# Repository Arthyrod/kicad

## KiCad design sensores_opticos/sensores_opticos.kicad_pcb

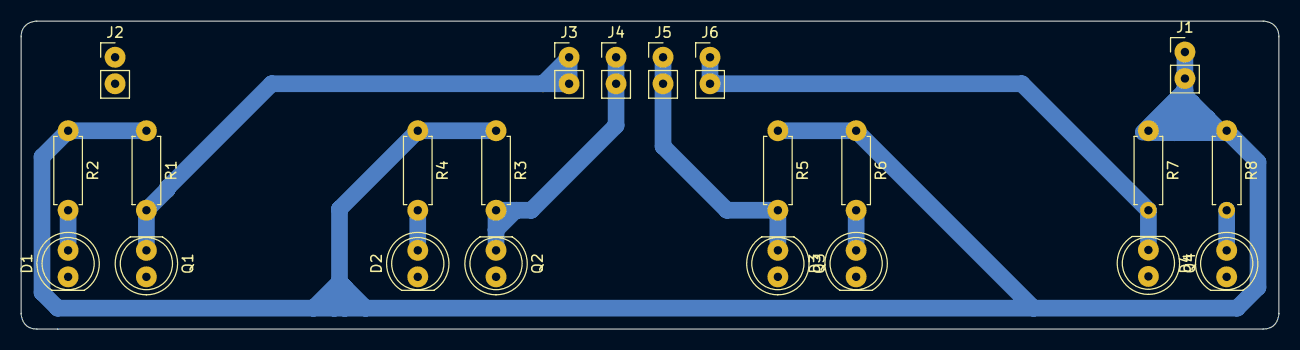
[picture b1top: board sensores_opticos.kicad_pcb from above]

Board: 2 copper layers, 120.5 x 29.5 mm, 22 parts (0 on the bottom side), 10 nets.

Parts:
D1, D2, D3, D4: LED; LED_D5.0mm
J1, J2, J3, J4, J5, J6: Conn_01x02_Pin; PinHeader_1x02_P2.54mm_Vertical
Q1, Q2, Q3, Q4: BPW40; LED_D5.0mm_Clear
R1, R2, R3, R4, R5, R6, R7, R8: R; R_Axial_DIN0207_L6.3mm_D2.5mm_P7.62mm_Horizontal

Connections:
+5V: J1.1, J1.2, R1.1, R2.1, R3.1, R4.1, R5.1, R6.1, R7.1, R8.1
GND: D1.1 (K), D2.1 (K), D3.1 (K), D4.1 (K), J2.1, J2.2, Q1.2 (E), Q2.2 (E), Q3.2 (E), Q4.2 (E)
unnamed: D1.2 (A), R2.2
unnamed: D2.2 (A), R4.2
unnamed: D3.2 (A), R6.2
unnamed: D4.2 (A), R8.2
unnamed: J3.1, J3.2, Q1.1 (C), R1.2
unnamed: J4.1, J4.2, Q2.1 (C), R3.2
unnamed: J5.1, J5.2, Q3.1 (C), R5.2
unnamed: J6.1, J6.2, Q4.1 (C), R7.2

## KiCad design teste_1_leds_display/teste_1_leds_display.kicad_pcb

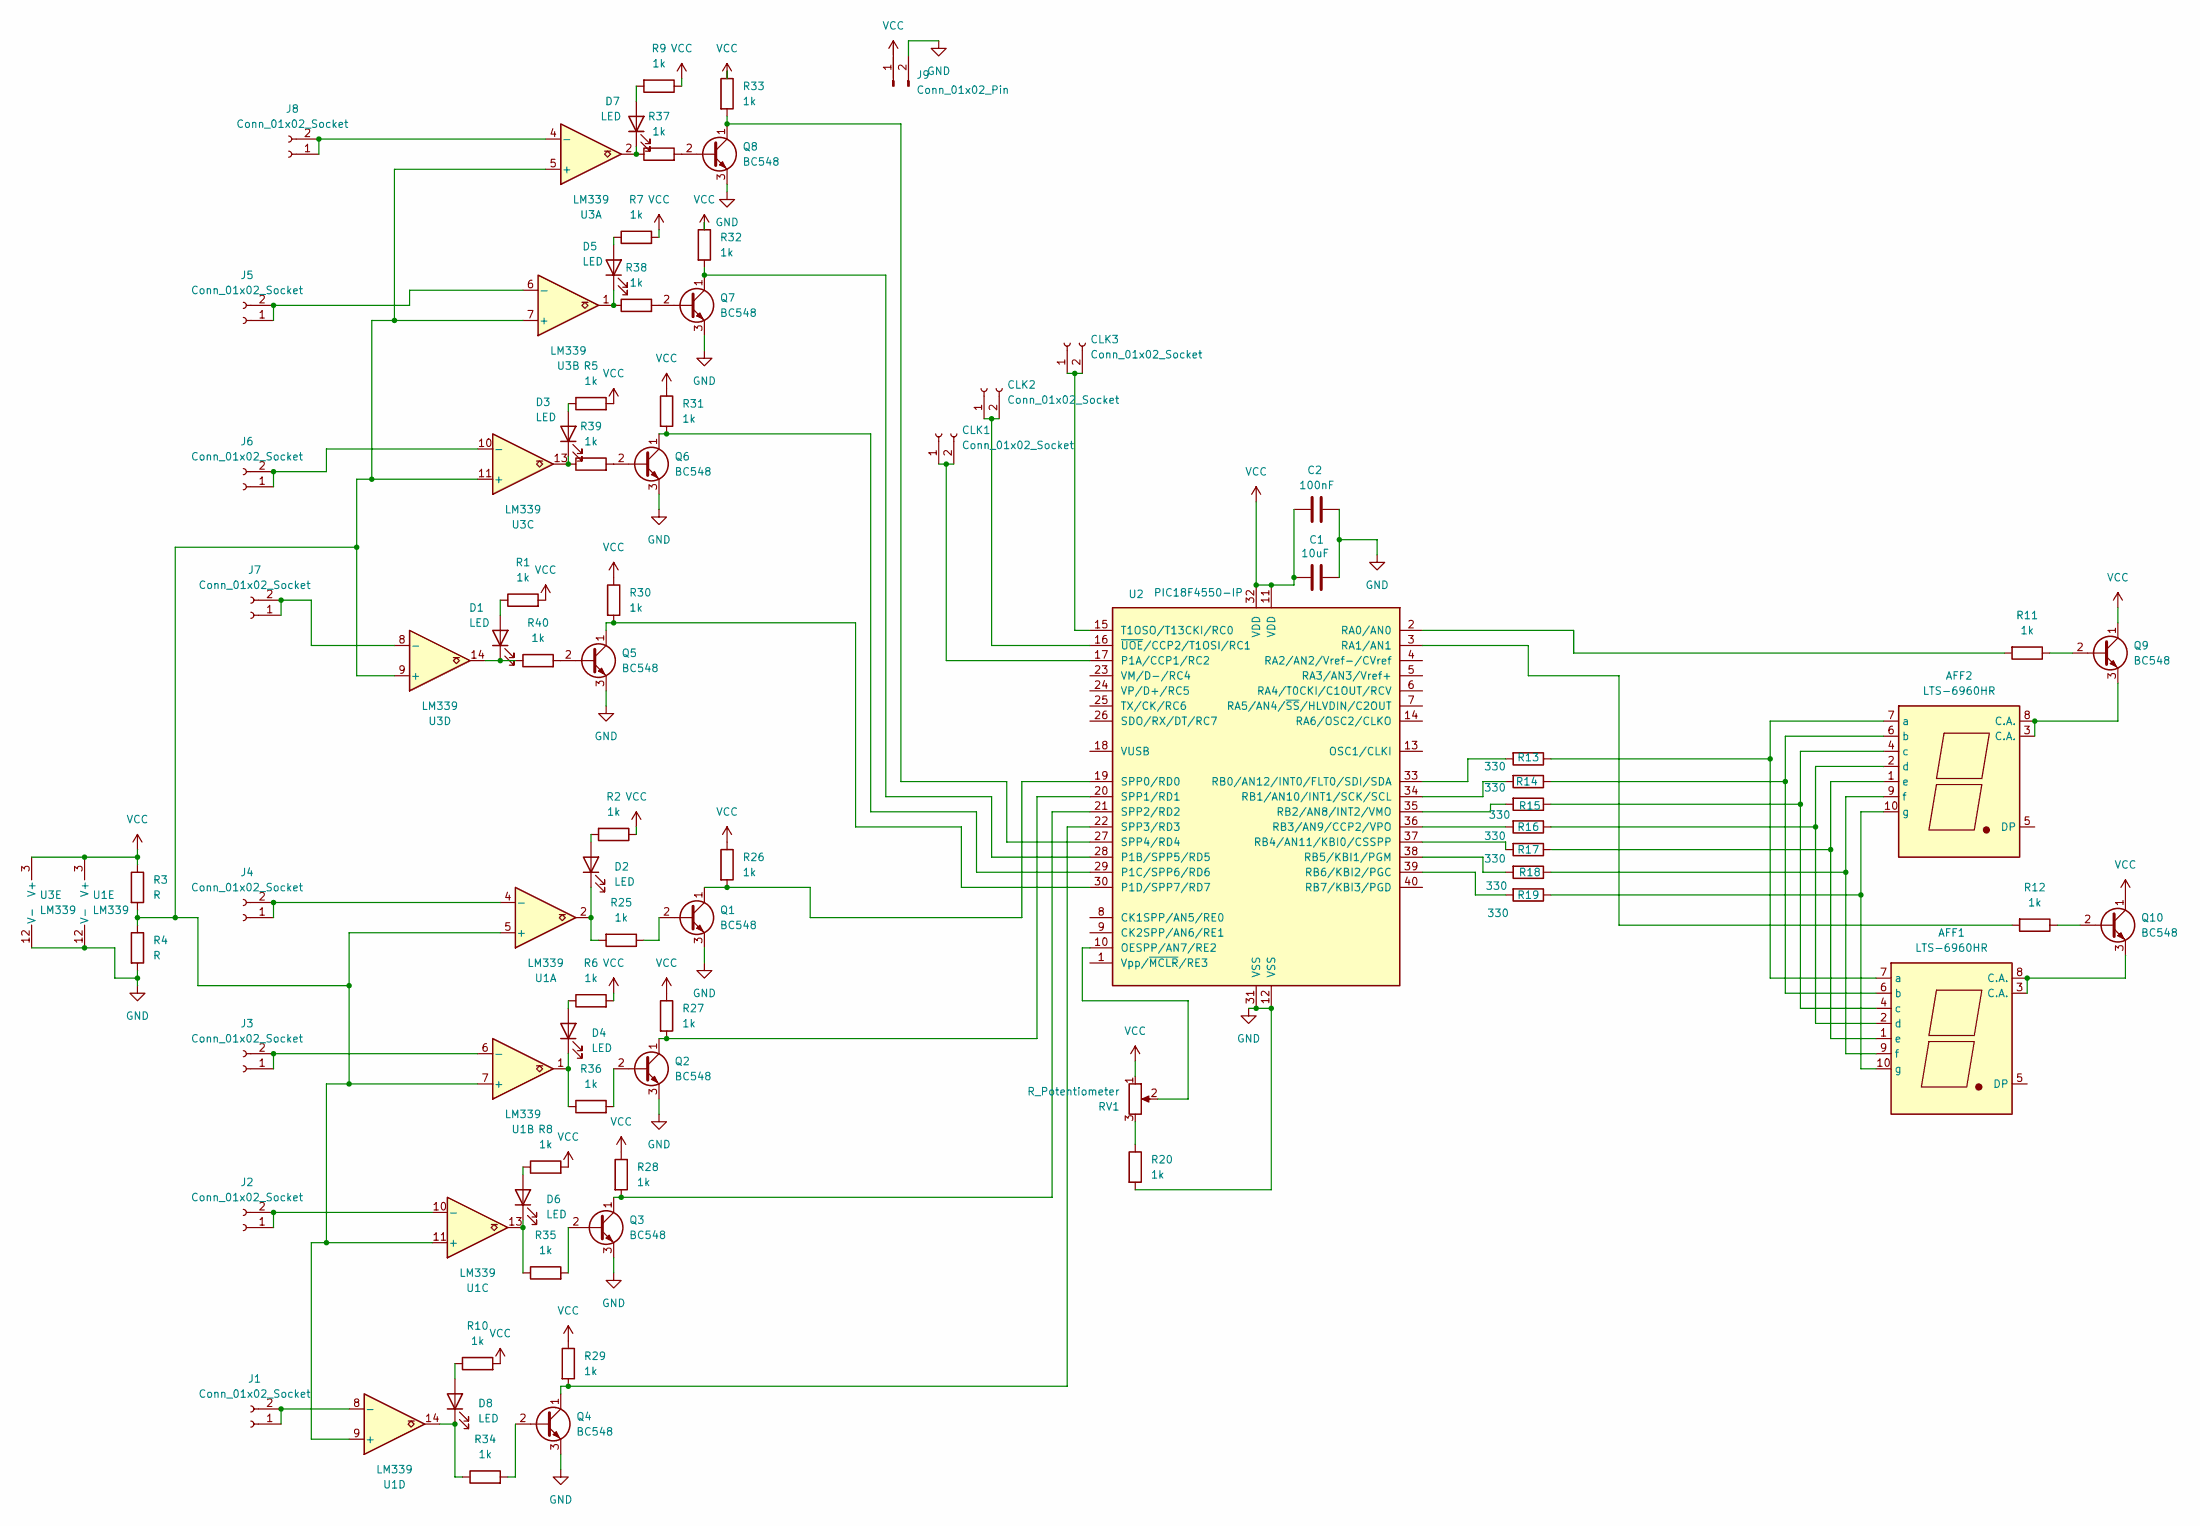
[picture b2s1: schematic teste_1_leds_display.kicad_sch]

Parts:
AFF1, AFF2: LTS-6960HR; 7SegmentLED_LTS6760_LTS6780
C1: 10uF; C_Axial_L5.1mm_D3.1mm_P7.50mm_Horizontal
C2: 100nF; C_Axial_L5.1mm_D3.1mm_P7.50mm_Horizontal
CLK1, CLK2, CLK3: Conn_01x02_Socket; PinSocket_1x02_P2.54mm_Vertical
D1, D2, D3, D4, D5, D6, D7, D8: LED; LED_D4.0mm
J1, J2, J3, J4, J5, J6, J7, J8: Conn_01x02_Socket; PinSocket_1x02_P2.54mm_Vertical
J9: Conn_01x02_Pin; PinHeader_1x02_P2.54mm_Vertical
Q1, Q2, Q3, Q4, Q5, Q6, Q7, Q8, Q9, Q10: BC548; TO-92_Wide
R1, R2, R5, R6, R7, R8, R9, R10, R11, R12, R20, R25, R26, R27, R28, R29, R30, R31, R32, R33, R34, R35, R36, R37, R38, R39, R40: 1k; R_Axial_DIN0207_L6.3mm_D2.5mm_P10.16mm_Horizontal
R3, R4: R; R_Axial_DIN0207_L6.3mm_D2.5mm_P10.16mm_Horizontal
R13, R14, R15, R16, R17, R18, R19: 330; R_Axial_DIN0207_L6.3mm_D2.5mm_P10.16mm_Horizontal
RV1: R_Potentiometer; Potentiometer_Alps_RK09K_Single_Vertical
U1, U3: LM339; DIP-14_W7.62mm
U2: PIC18F4550-IP; DIP-40_W15.24mm

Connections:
GND: C1.2, C2.2, J9.2, Q1.3 (E), Q2.3 (E), Q3.3 (E), Q4.3 (E), Q5.3 (E), Q6.3 (E), Q7.3 (E), Q8.3 (E), R4.2, R20.2, U1.12 (V-), U2.12 (VSS), U2.31 (VSS), U3.12 (V-)
unnamed: AFF1.7 (a), AFF2.7 (a), R13.1
unnamed: AFF1.6 (b), AFF2.6 (b), R14.1
unnamed: AFF1.4 (c), AFF2.4 (c), R15.1
unnamed: AFF1.2 (d), AFF2.2 (d), R16.1
unnamed: AFF1.1 (e), AFF2.1 (e), R17.1
unnamed: AFF1.9 (f), AFF2.9 (f), R18.1
unnamed: AFF1.10 (g), AFF2.10 (g), R19.1
unnamed 8: CLK1.1, CLK1.2, U2.17 (P1A/CCP1/RC2); also elsewhere on the board
unnamed 9: CLK2.1, CLK2.2, U2.16 (~UOE/CCP2/T1OSI/RC1); also elsewhere on the board
unnamed 10: CLK3.1, CLK3.2, U2.15 (T1OSO/T13CKI/RC0); also elsewhere on the board
unnamed: D1.2 (A), R1.1
unnamed: D1.1 (K), R40.1, U3.14
unnamed: D2.2 (A), R2.2
unnamed: D2.1 (K), R25.2, U1.2
unnamed: D3.2 (A), R5.1
unnamed: D3.1 (K), R39.1, U3.13
unnamed: D4.2 (A), R6.1
unnamed: D4.1 (K), R36.1, U1.1
unnamed: D5.2 (A), R7.1
unnamed: D5.1 (K), R38.1, U3.1
unnamed: D6.2 (A), R8.1
unnamed: D6.1 (K), R35.1, U1.13
unnamed: D7.2 (A), R9.2
unnamed: D7.1 (K), R37.1, U3.2
unnamed: D8.2 (A), R10.1
unnamed: D8.1 (K), R34.1, U1.14
unnamed: J1.1, J1.2, U1.8 (-)
unnamed: J2.1, J2.2, U1.10 (-)
unnamed: J3.1, J3.2, U1.6 (-)
unnamed: J4.1, J4.2, U1.4 (-)
unnamed: J5.1, J5.2, U3.6 (-)
unnamed: J6.1, J6.2, U3.10 (-)
unnamed: J7.1, J7.2, U3.8 (-)
unnamed: J8.1, J8.2, U3.4 (-)
unnamed: Q1.2 (B), R25.1
unnamed: Q1.1 (C), R26.2, U2.19 (SPP0/RD0)
unnamed: Q2.2 (B), R36.2
unnamed: Q2.1 (C), R27.2, U2.20 (SPP1/RD1)
unnamed: Q3.2 (B), R35.2
unnamed: Q3.1 (C), R28.2, U2.21 (SPP2/RD2)
unnamed: Q4.2 (B), R34.2
unnamed: Q4.1 (C), R29.2, U2.22 (SPP3/RD3)
unnamed: Q5.2 (B), R40.2
unnamed: Q5.1 (C), R30.2, U2.30 (P1D/SPP7/RD7)
unnamed: Q6.2 (B), R39.2
unnamed: Q6.1 (C), R31.2, U2.29 (P1C/SPP6/RD6)
unnamed: Q7.2 (B), R38.2
unnamed: Q7.1 (C), R32.2, U2.28 (P1B/SPP5/RD5)
unnamed: Q8.2 (B), R37.2
unnamed: Q8.1 (C), R33.2, U2.27 (SPP4/RD4)
unnamed: Q9.2 (B), R11.1
unnamed: AFF2.3 (C.A.), AFF2.8 (C.A.), Q9.3 (E)
unnamed: Q10.2 (B), R12.1
unnamed: AFF1.3 (C.A.), AFF1.8 (C.A.), Q10.3 (E)
unnamed: R20.1, RV1.3
unnamed: R3.2, R4.1, U1.5 (+), U1.7 (+), U1.9 (+), U1.11 (+), U3.5 (+), U3.7 (+), U3.9 (+), U3.11 (+)
unnamed: RV1.2, U2.10 (OESPP/AN7/RE2)
unnamed: R11.2, U2.2 (RA0/AN0)
unnamed: R12.2, U2.3 (RA1/AN1)
unnamed: R13.2, U2.33 (RB0/AN12/INT0/FLT0/SDI/SDA)
unnamed: R14.2, U2.34 (RB1/AN10/INT1/SCK/SCL)
unnamed: R15.2, U2.35 (RB2/AN8/INT2/VMO)
unnamed: R16.2, U2.36 (RB3/AN9/CCP2/VPO)
unnamed: R17.2, U2.37 (RB4/AN11/KBI0/CSSPP)
unnamed: R18.2, U2.38 (RB5/KBI1/PGM)
unnamed: R19.2, U2.39 (RB6/KBI2/PGC)
VCC: C1.1, C2.1, J9.1, Q9.1 (C), Q10.1 (C), R1.2, R2.1, R3.1, R5.2, R6.2, R7.2, R8.2, R9.1, R10.2, R26.1, R27.1, R28.1, R29.1, R30.1, R31.1, R32.1, R33.1, RV1.1, U1.3 (V+), U2.11 (VDD), U2.32 (VDD), U3.3 (V+)

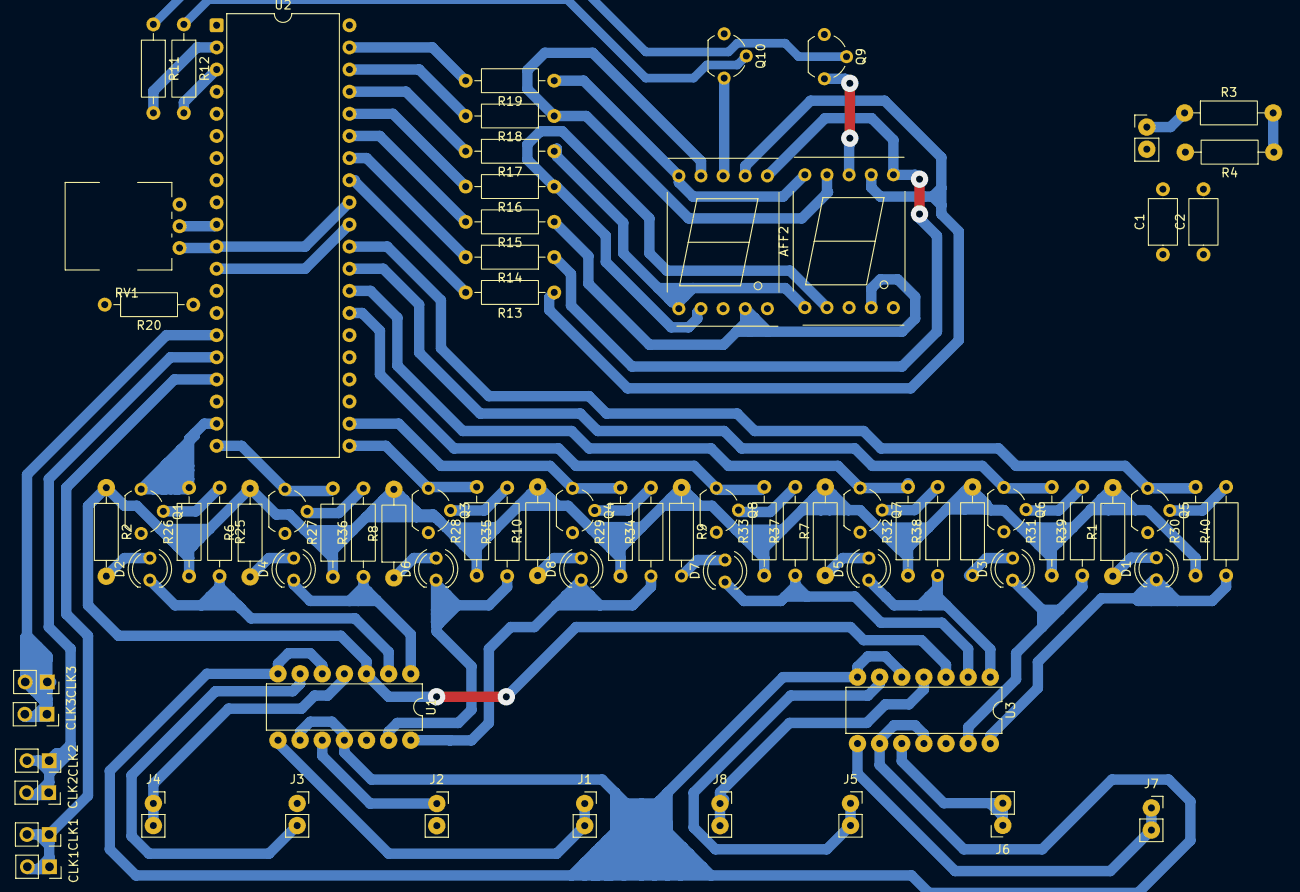
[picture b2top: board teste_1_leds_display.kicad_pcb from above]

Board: 2 copper layers, 77 parts (0 on the bottom side), 68 nets.

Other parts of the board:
CLK1#2, CLK2#2, CLK3#2: Conn_01x02_Socket; PinSocket_1x02_P2.54mm_Vertical

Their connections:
unnamed 8: CLK1#2.1, CLK1#2.2; also elsewhere on the board
unnamed 9: CLK2#2.1, CLK2#2.2; also elsewhere on the board
unnamed 10: CLK3#2.1, CLK3#2.2; also elsewhere on the board
